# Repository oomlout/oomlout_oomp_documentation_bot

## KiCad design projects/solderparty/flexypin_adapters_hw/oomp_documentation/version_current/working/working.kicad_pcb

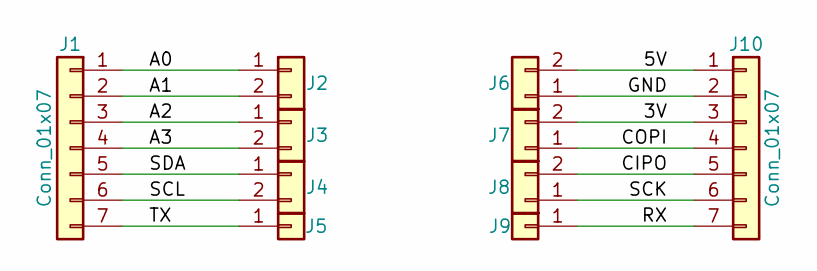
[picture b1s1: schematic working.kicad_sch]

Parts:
J1, J10: Conn_01x07; PinHeader_1x07_P2.54mm_Vertical
J2, J3, J4, J6, J7, J8: Conn_01x02; FlexyPin_1x02_P2.54mm
J5, J9: Conn_01x01; FlexyPin_1x01_P2.54mm

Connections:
/3V: J7.2, J10.3
/5V: J6.2, J10.1
/A0: J1.1, J2.1
/A1: J1.2, J2.2
/A2: J1.3, J3.1
/A3: J1.4, J3.2
/CIPO: J8.2, J10.5
/COPI: J7.1, J10.4
/GND: J6.1, J10.2
/RX: J9.1, J10.7
/SCK: J8.1, J10.6
/SCL: J1.6, J4.2
/SDA: J1.5, J4.1
/TX: J1.7, J5.1

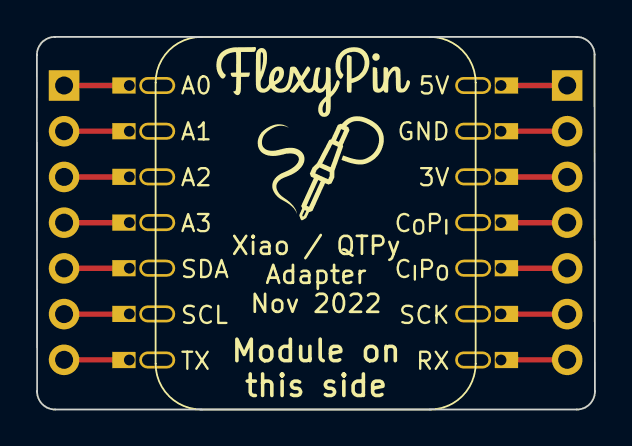
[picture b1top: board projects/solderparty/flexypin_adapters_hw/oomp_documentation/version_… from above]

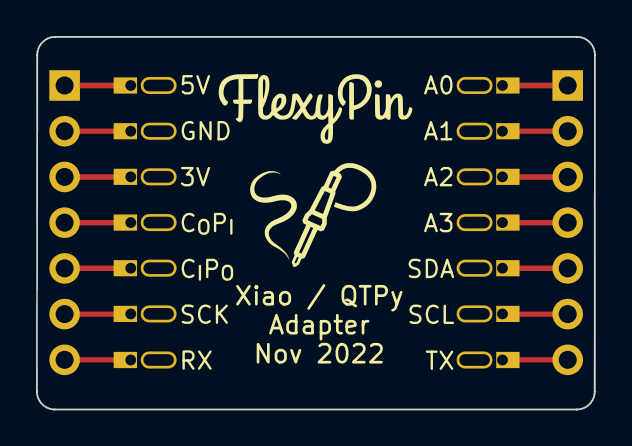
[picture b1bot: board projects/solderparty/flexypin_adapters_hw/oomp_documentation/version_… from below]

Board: 2 copper layers, 31.0 x 20.7 mm, 10 parts (2 on the bottom side), 14 nets.

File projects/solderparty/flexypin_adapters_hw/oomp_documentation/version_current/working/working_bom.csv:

"Id";"Designator";"Footprint";"Quantity";"Designation";"Supplier and ref";
1;"J4,J8,J7,J2,J3,J6";"FlexyPin_1x02_P2.54mm";6;"Conn_01x02";;;
2;"REF**";"Fiducial_0.5mm_Mask1.5mm";1;"Fiducial_0.5mm_Mask1.5mm";;;
3;"J5,J9";"FlexyPin_1x01_P2.54mm";2;"Conn_01x01";;;
4;"G***,G***";"SolderParty-New-Logo_7.5x6.4mm_SilkScreen";2;"LOGO";;;
5;"J10,J1";"PinHeader_1x07_P2.54mm_Vertical";2;"Conn_01x07";;;

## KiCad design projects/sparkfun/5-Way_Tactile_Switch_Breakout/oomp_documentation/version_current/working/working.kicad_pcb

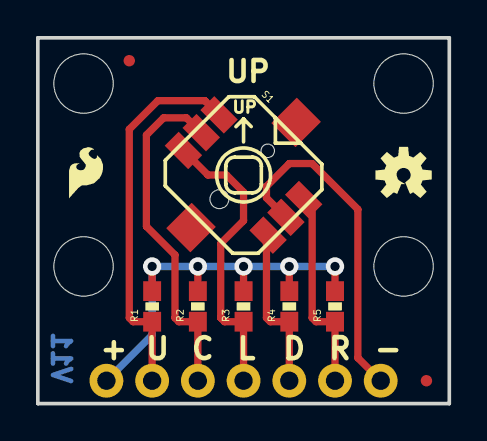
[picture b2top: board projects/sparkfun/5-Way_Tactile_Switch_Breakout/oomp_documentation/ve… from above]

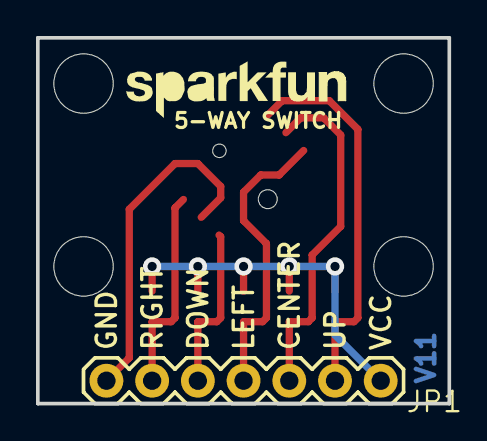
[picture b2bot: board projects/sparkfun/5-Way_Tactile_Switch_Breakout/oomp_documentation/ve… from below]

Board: 2 copper layers, 22.9 x 20.3 mm, 17 parts (2 on the bottom side), 7 nets.

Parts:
JP1: 1X07
JP2, JP7: FIDUCIALUFIDUCIAL; MICRO-FIDUCIAL
JP3, JP4, JP5, JP6: STAND-OFF
JP9: LOGO-SFESK; SFE-LOGO-FLAME
JP10: LOGO-SFENW2; SFE-NEW-WEB
R1, R2, R3, R4, R5: 10K; 0603-RES
S1: 5-WAY-TACTILE-SWITCH; JOYSTICK_MINI
U$1: OSHW-LOGOS; OSHW-LOGO-S
U$2: CREATIVE_COMMONS

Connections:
CENTER: JP1.3, R2.1, S1.CTR
DOWN: JP1.5, R4.1, S1.D
GND: JP1.7, S1.GND
LEFT: JP1.4, R3.1, S1.C
RIGHT: JP1.6, R5.1, S1.B
UP: JP1.2, R1.1, S1.A
VCC: JP1.1, R1.2, R2.2, R3.2, R4.2, R5.2

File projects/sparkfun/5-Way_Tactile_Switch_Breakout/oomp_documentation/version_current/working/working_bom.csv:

"Id";"Designator";"Footprint";"Quantity";"Designation";"Supplier and ref";
1;"JP7,JP2";"MICRO-FIDUCIAL";2;"FIDUCIALUFIDUCIAL";;;
2;"R3,R1,R2,R5,R4";"0603-RES";5;"10K";;;
3;"U$1";"OSHW-LOGO-S";1;"OSHW-LOGOS";;;
4;"U$2";"CREATIVE_COMMONS";1;"CREATIVE_COMMONS";;;
5;"JP5,JP6,JP3,JP4";"STAND-OFF";4;"STAND-OFF";;;
6;"JP9";"SFE-LOGO-FLAME";1;"LOGO-SFESK";;;
7;"S1";"JOYSTICK_MINI";1;"5-WAY-TACTILE-SWITCH";;;
8;"JP1";"1X07";1;"";;;
9;"JP10";"SFE-NEW-WEB";1;"LOGO-SFENW2";;;

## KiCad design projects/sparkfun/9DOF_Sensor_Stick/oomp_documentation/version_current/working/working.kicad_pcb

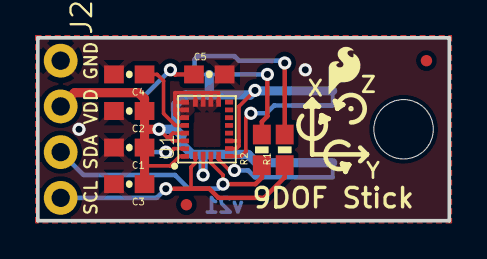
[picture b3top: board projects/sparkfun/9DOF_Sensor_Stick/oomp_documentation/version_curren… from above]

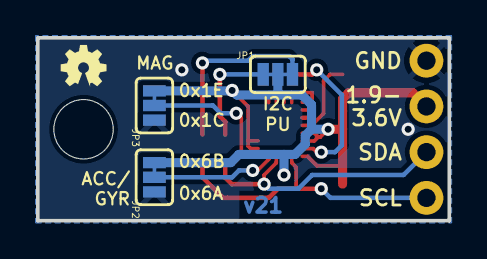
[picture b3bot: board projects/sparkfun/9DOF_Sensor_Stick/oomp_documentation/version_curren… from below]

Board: 2 copper layers, 22.9 x 10.2 mm, 18 parts (4 on the bottom side), 10 nets.

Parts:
C1: 10uF; 0603-CAP
C2, C3, C5: 0.1uF; 0603-CAP
C4: 10nF; 0603-CAP
FD3, FD4: FIDUCIALUFIDUCIAL; MICRO-FIDUCIAL
FRAME1: FRAME-LETTER; CREATIVE_COMMONS
H1: STAND-OFF
J2: 1X04_NO_SILK_ALL_ROUND
JP1: PAD-JUMPER-3-3OF3_NC_BY_TRACE_YES_SILK_FULL_BOX
JP2, JP3: PAD-JUMPER-3-2OF3_NC_BY_TRACE_YES_SILK_FULL_BOX
LOGO1: SFE_LOGO_FLAME.1_INCH; SFE_LOGO_FLAME_.1
LOGO3: OSHW-LOGOMINI; OSHW-LOGO-MINI
R1, R2: 4.7K; 0603-RES
U1: LSM9DS1; LGA24-8X4

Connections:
GND: C1.2, C2.2, C3.2, C4.2, C5.2, J2.1, JP2.1, JP3.1, U1.14, U1.15, U1.16, U1.17, U1.18, U1.19, U1.20
unnamed: JP1.1, R2.2
unnamed: JP1.3, R1.2
unnamed: C4.1, U1.21
unnamed: C5.1, U1.24
SCL: J2.4, R1.1, U1.2
SDA: J2.3, R2.1, U1.4
SDO_A/G: JP2.2, U1.5
SDO_M: JP3.2, U1.6
VDD: C1.1, C2.1, C3.1, J2.2, JP1.2, JP2.3, JP3.3, U1.1, U1.3, U1.7, U1.8, U1.22, U1.23

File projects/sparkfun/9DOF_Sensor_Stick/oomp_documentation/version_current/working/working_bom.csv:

"Id";"Designator";"Footprint";"Quantity";"Designation";"Supplier and ref";
1;"R2,R1";"0603-RES";2;"4.7K";;;
2;"C3,C2,C5";"0603-CAP";3;"0.1uF";;;
3;"FRAME1";"CREATIVE_COMMONS";1;"FRAME-LETTER";;;
4;"FD3,FD4";"MICRO-FIDUCIAL";2;"FIDUCIALUFIDUCIAL";;;
5;"LOGO1";"SFE_LOGO_FLAME_.1";1;"SFE_LOGO_FLAME.1_INCH";;;
6;"U1";"LGA24-8X4";1;"LSM9DS1";;;
7;"J2";"1X04_NO_SILK_ALL_ROUND";1;"";;;
8;"C1";"0603-CAP";1;"10uF";;;
9;"C4";"0603-CAP";1;"10nF";;;
10;"H1";"STAND-OFF";1;"STAND-OFF";;;
11;"LOGO3";"OSHW-LOGO-MINI";1;"OSHW-LOGOMINI";;;
12;"JP1";"PAD-JUMPER-3-3OF3_NC_BY_TRACE_YES_SILK_FULL_BOX";1;"";;;
13;"JP3,JP2";"PAD-JUMPER-3-2OF3_NC_BY_TRACE_YES_SILK_FULL_BOX";2;"";;;

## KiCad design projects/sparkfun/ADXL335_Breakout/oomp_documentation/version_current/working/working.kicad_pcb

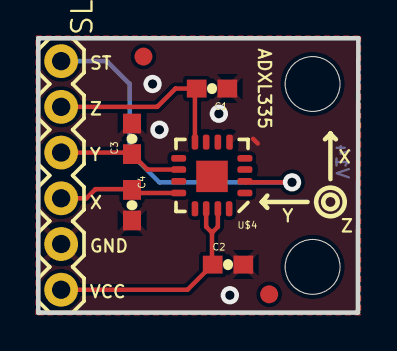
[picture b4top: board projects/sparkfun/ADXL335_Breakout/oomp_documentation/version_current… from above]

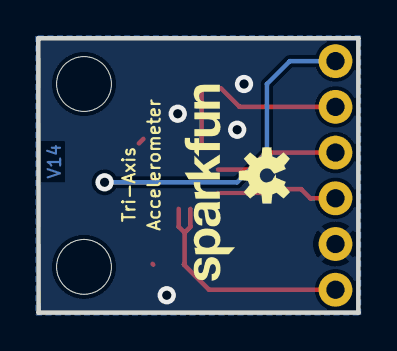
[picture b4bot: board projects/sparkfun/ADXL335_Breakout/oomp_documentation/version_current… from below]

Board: 16 copper layers, 17.8 x 15.2 mm, 12 parts (2 on the bottom side), 6 nets.

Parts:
C1, C2, C3, C4: 0.1uF; 0603-CAP
SL1: 1X06
U$1, U$3: FIDUCIAL1X2; FIDUCIAL-1X2
U$4: ADXL335-PATRICK""; ADXL335-P
U$5: OSHW-LOGO-S
U$6, U$7: STAND-OFF-TIGHT
U$8: SFE_LOGO_NAME_.1

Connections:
GND: C1.1, C2.2, C3.2, C4.2, SL1.5, U$4.3, U$4.5, U$4.6, U$4.7
ST: SL1.1, U$4.2
VCC: C2.1, SL1.6, U$4.14, U$4.15
XOUT: C4.1, SL1.4, U$4.12
YOUT: C3.1, SL1.3, U$4.10
ZOUT: C1.2, SL1.2, U$4.8

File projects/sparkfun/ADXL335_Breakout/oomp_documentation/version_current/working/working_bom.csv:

"Id";"Designator";"Footprint";"Quantity";"Designation";"Supplier and ref";
1;"C4,C3,C1,C2";"0603-CAP";4;"0.1uF";;;
2;"U$7,U$6";"STAND-OFF-TIGHT";2;"";;;
3;"U$3,U$1";"FIDUCIAL-1X2";2;"FIDUCIAL1X2";;;
4;"U$4";"ADXL335-P";1;"ADXL335-PATRICK""";;;
5;"SL1";"1X06";1;"";;;
6;"U$8";"SFE_LOGO_NAME_.1";1;"";;;
7;"U$5";"OSHW-LOGO-S";1;"";;;

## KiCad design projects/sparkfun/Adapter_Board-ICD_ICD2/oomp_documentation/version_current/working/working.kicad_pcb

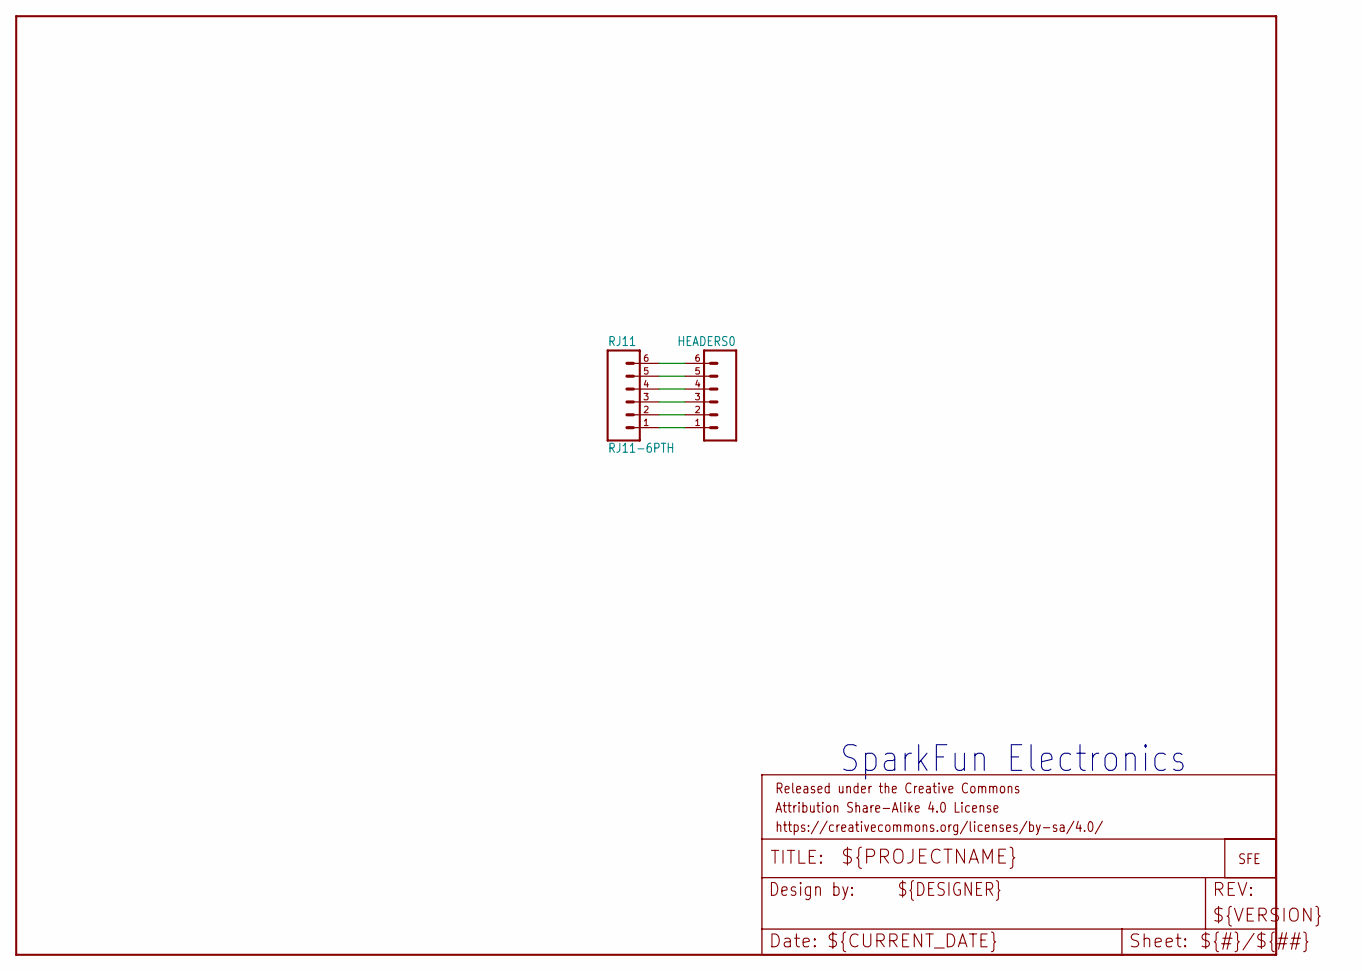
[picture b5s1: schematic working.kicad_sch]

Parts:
FRAME1: FRAME-LETTERNO_PACKAGE; DUMMY
HEADERS0: M06POLAR; MOLEX-1X6
JP1: LOGO-SFESK; SFE-LOGO-FLAME
RJ11: RJ11-6PTH; RJ11-6

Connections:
unnamed: HEADERS0.6, RJ11.6
unnamed: HEADERS0.1, RJ11.1
unnamed: HEADERS0.2, RJ11.2
unnamed: HEADERS0.3, RJ11.3
unnamed: HEADERS0.4, RJ11.4
unnamed: HEADERS0.5, RJ11.5

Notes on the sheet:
SparkFun Electronics

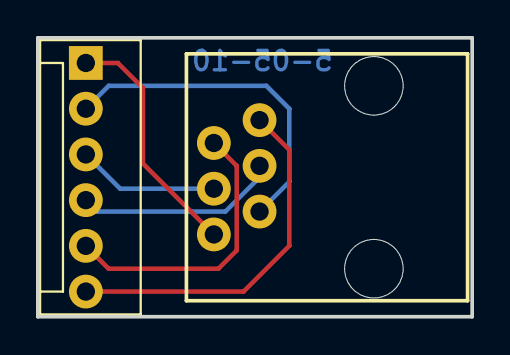
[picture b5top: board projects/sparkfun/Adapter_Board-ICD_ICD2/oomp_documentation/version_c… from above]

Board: 16 copper layers, 24.1 x 15.5 mm, 4 parts (1 on the bottom side), 6 nets.

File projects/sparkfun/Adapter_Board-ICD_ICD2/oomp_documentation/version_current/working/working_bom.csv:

"Id";"Designator";"Footprint";"Quantity";"Designation";"Supplier and ref";
1;"RJ11";"RJ11-6";1;"RJ11-6PTH";;;
2;"FRAME1";"DUMMY";1;"";;;
3;"HEADERS0";"MOLEX-1X6";1;"";;;
4;"JP1";"SFE-LOGO-FLAME";1;"LOGO-SFESK";;;

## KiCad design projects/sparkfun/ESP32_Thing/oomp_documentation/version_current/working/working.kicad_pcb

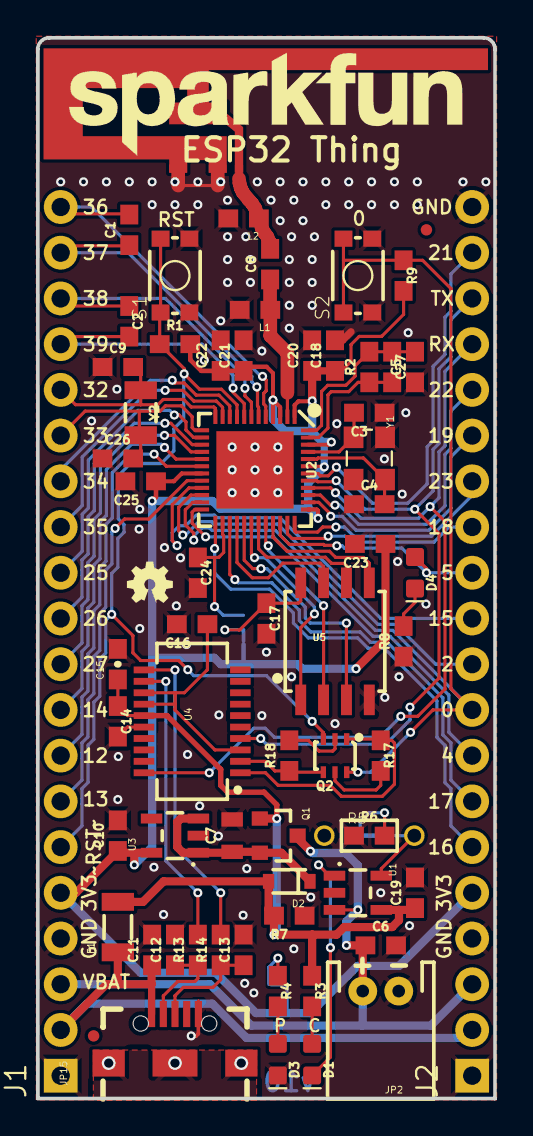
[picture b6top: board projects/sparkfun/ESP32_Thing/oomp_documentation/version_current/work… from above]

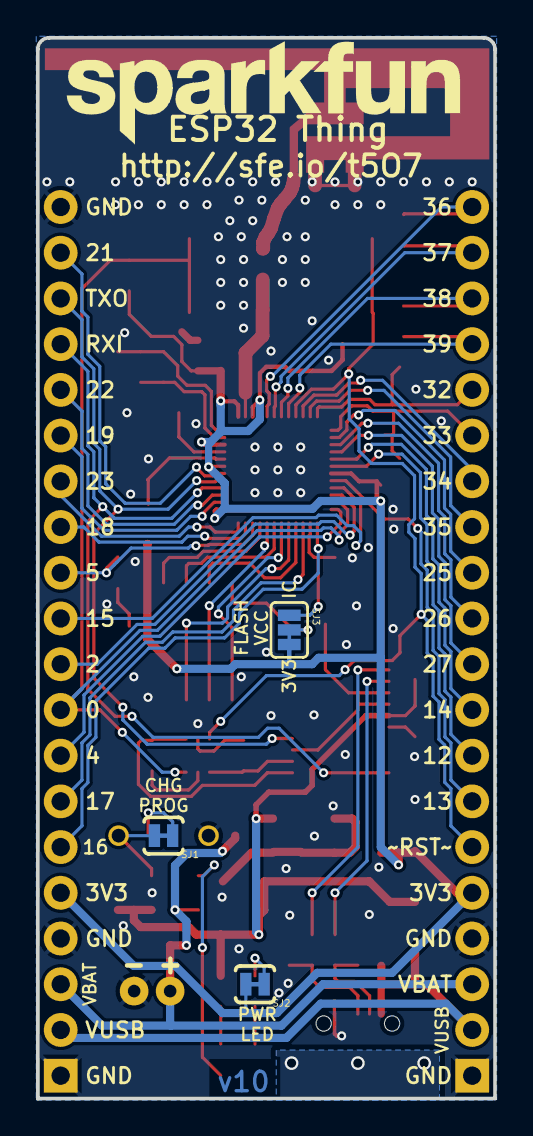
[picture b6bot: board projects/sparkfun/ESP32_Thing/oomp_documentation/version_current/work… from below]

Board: 2 copper layers, 25.4 x 58.9 mm, 72 parts (4 on the bottom side), 66 nets.

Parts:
C1, C2: 270pF; 0603
C3, C4: 10pF; 0603
C5: 10nF; 0603
C6, C19: 4.7uF; 0603
C7: 1.0uF; 0805
C8: 5.6pF; 0603
C9, C26: 15pF; 0603
C10: 2.2uF; 0603
C11, C14, C16, C17, C20, C21, C23, C25: 0.1uF; 0603
C12, C13: 47pF; 0603
C15: 4.7uF; 0603-CAP
C18: 100pF; 0603
C22: 10uF; 0603
C24: 1.0uF; 0603
C27: 3.0nF; 0603
D1: Yellow; LED-0603
D2: BAT20J; SOD-323
D3: RED; LED-0603
D4: BLUE; LED-0603
E1: ANTENNA; TRACE_ANTENNA_2.4GHZ_25.7MM_TUNED
F1: 500mA; PTC-1206
FD1, FD2: FIDUCIALUFIDUCIAL; MICRO-FIDUCIAL
FRAME1: FRAME-LEDGER; CREATIVE_COMMONS
J1, J2: 1X20_NOSILK
JP2: LiPo; JST-2-PTH
JP15: USB-B-MICRO-SMD_V03
L1, L2: DNP; 0603
LOGO1, LOGO3: SFE_LOGO_NAME.2_INCH; SFE_LOGO_NAME_.2
LOGO2: OSHW-LOGOMINI; OSHW-LOGO-MINI
Q1: 2.5A/30V; SOT23-3
Q2: MBT3904DW1T1; SC70-6
R1, R7, R9, R17, R18: 10k; 0603
R2: 20k; 0603
R3, R4: 1K; 0603
R5: DNP; 1_6W-RES
R6: 2.0k; 0603
R8: 330; 0603
R13, R14: 27; 0603
S1: RESET; TACTILE_SWITCH_SMD_4.6X2.8MM
S2: BTN-0; TACTILE_SWITCH_SMD_4.6X2.8MM
SJ1, SJ2: JUMPER-PAD-2-NC_BY_TRACE; PAD-JUMPER-2-NC_BY_TRACE_YES_SILK
SJ3: PAD-JUMPER-3-2OF3_NC_BY_TRACE_YES_SILK_FULL_BOX
U1: MCP73831; SOT23-5
U2: ESP3212; QFN48-0.4MM
U3: AP2112K-3.3V; SOT23-5
U4: FT231XS; SSOP20_L
U5: W25Q32FVSS; SOIC-8
Y1: 26MHz; CRYSTAL-SMD-3.2X2.5
Y2: 32.768kHz; CRYSTAL-SMD-3.2X1.5MM

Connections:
0: J2.9, Q2.6, R9.1, S2.3, S2.4, U2.23
2: J2.10, U2.22
3.3V: C10.1, C18.1, C20.1, C21.1, C22.1, C23.1, C25.1, J1.5, J2.5, R1.2, R9.2, SJ2.2, SJ3.3, U2.1, U2.3, U2.4, U2.19, U2.37, U2.43, U2.46, U3.5
3.3V_F: C16.1, U4.3, U4.13, U4.14
4: J2.8, U2.24
5: D4.A, J2.12, U2.34
12: J1.8, U2.18
13: J1.7, U2.20
14: J1.9, U2.17
15: J2.11, U2.21
16: J2.6, U2.25
17: J2.7, U2.27
18: J2.13, U2.35
19: J2.15, U2.38
21: J2.19, U2.42
22: J2.16, U2.39
23: J2.14, U2.36
25: J1.12, U2.14
26: J1.11, U2.15
27: J1.10, U2.16
32K_XN: C26.2, J1.15, U2.13, Y2.P$2
32K_XP: C9.2, J1.16, U2.12, Y2.P$1
34: J1.14, U2.10
35: J1.13, U2.11
36: C1.2, J1.20, U2.5
37: C1.1, J1.19, U2.6
38: C2.1, J1.18, U2.7
39: C2.2, J1.17, U2.8
CAP_10N: C5.2, C27.1, R2.2, U2.48
CHIP_PU: J1.6, Q2.3, R1.1, S1.3, S1.4, U2.9
D+: C13.1, JP15.D+, R14.1
D-: C12.1, JP15.D-, R13.1
DTR: Q2.1, R17.1, U4.1
FLASH_SCK: U2.31, U5.6
FLASH_SCS: U2.30, U5.1
FLASH_SDI: U2.33, U5.5
FLASH_SDO: U2.32, U5.2
FLASH_SHD: U2.28, U5.7
FLASH_SWP: U2.29, U5.3
FLASH_VDD: C24.1, SJ3.1, U2.26
GND: C3.1, C4.1, C5.1, C6.2, C7.2, C9.1, C10.2, C11.2, C12.2, C13.2, C14.2, C15.2, C16.2, C17.2, C18.2, C19.2, C20.2, C21.2, C22.2, C23.2, C24.2, C25.2, C26.1, D3.C, E1.GND, E1.GND2, J1.1, J1.4, J2.1, J2.4, J2.20, JP2.1, JP15.GND, L1.2, L2.2, R5.1, R6.1, R7.1, R8.1, S1.1, S1.2, S2.1, S2.2, U1.2, U2.EP, U3.2, U4.6, U4.16, U5.4, Y1.2, Y1.4
LNA_IN: C8.1, L1.1, U2.2
unnamed: D4.C, R8.2
unnamed: D3.A, R4.2
unnamed: R4.1, SJ2.1
unnamed: C27.2, R2.1, U2.47
unnamed: R13.2, U4.12
unnamed: R14.2, U4.11
unnamed: D1.C, U1.1
unnamed: Q2.5, R17.2
unnamed: C17.1, SJ3.2, U5.8
unnamed: Q2.2, R18.2
unnamed: C3.2, U2.45, Y1.1
unnamed: R5.2, SJ1.2, U1.5
unnamed: C4.2, U2.44, Y1.3
unnamed: R6.2, SJ1.1
unnamed: D1.A, R3.2
RTS: Q2.4, R18.1, U4.2
SHIELD: JP15.SHIELD1, JP15.SHIELD2, JP15.SHIELD3
TRACE_ANT: C8.2, E1.ANT, L2.1
U0RXD: J2.17, U2.40, U4.20
U0TXD: J2.18, U2.41, U4.4
VIN: C7.1, D2.C, Q1.2, U3.1, U3.3
VUSB-RAW: C11.1, F1.1, J1.2, J2.2, JP15.VBUS
V_BATT: C6.1, J1.3, J2.3, JP2.2, Q1.3, U1.3
V_USB: C14.1, C15.1, C19.1, D2.A, F1.2, Q1.1, R3.1, R7.2, U1.4, U4.15

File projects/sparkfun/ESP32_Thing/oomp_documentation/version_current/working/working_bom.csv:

"Id";"Designator";"Footprint";"Quantity";"Designation";"Supplier and ref";
1;"R3,R4";"0603";2;"1K";;;
2;"U5";"SOIC-8";1;"W25Q32FVSS";;;
3;"C10";"0603";1;"2.2uF";;;
4;"R1,R9,R17,R7,R18";"0603";5;"10k";;;
5;"JP15";"USB-B-MICRO-SMD_V03";1;"";;;
6;"R14,R13";"0603";2;"27";;;
7;"C20,C14,C25,C17,C16,C23,C11,C21";"0603";8;"0.1uF";;;
8;"C13,C12";"0603";2;"47pF";;;
9;"C8";"0603";1;"5.6pF";;;
10;"C26,C9";"0603";2;"15pF";;;
11;"C1,C2";"0603";2;"270pF";;;
12;"C19,C6";"0603";2;"4.7uF";;;
13;"C18";"0603";1;"100pF";;;
14;"L2,L1";"0603";2;"DNP";;;
15;"J1,J2";"1X20_NOSILK";2;"";;;
16;"R5";"1_6W-RES";1;"DNP";;;
17;"C3,C4";"0603";2;"10pF";;;
18;"Y2";"CRYSTAL-SMD-3.2X1.5MM";1;"32.768kHz";;;
19;"C22";"0603";1;"10uF";;;
20;"Q1";"SOT23-3";1;"2.5A/30V";;;
21;"C15";"0603-CAP";1;"4.7uF";;;
22;"C27";"0603";1;"3.0nF";;;
23;"U1";"SOT23-5";1;"MCP73831";;;
24;"S2";"TACTILE_SWITCH_SMD_4.6X2.8MM";1;"BTN-0";;;
25;"FD2,FD1";"MICRO-FIDUCIAL";2;"FIDUCIALUFIDUCIAL";;;
26;"D4";"LED-0603";1;"BLUE";;;
27;"F1";"PTC-1206";1;"500mA";;;
28;"C7";"0805";1;"1.0uF";;;
29;"U3";"SOT23-5";1;"AP2112K-3.3V";;;
30;"R2";"0603";1;"20k";;;
31;"E1";"TRACE_ANTENNA_2.4GHZ_25.7MM_TUNED";1;"ANTENNA";;;
32;"D3";"LED-0603";1;"RED";;;
33;"Q2";"SC70-6";1;"MBT3904DW1T1";;;
34;"LOGO2";"OSHW-LOGO-MINI";1;"OSHW-LOGOMINI";;;
35;"D1";"LED-0603";1;"Yellow";;;
36;"R8";"0603";1;"330";;;
37;"S1";"TACTILE_SWITCH_SMD_4.6X2.8MM";1;"RESET";;;
38;"U4";"SSOP20_L";1;"FT231XS";;;
39;"U2";"QFN48-0.4MM";1;"ESP3212";;;
40;"JP2";"JST-2-PTH";1;"LiPo";;;
41;"Y1";"CRYSTAL-SMD-3.2X2.5";1;"26MHz";;;
42;"FRAME1";"CREATIVE_COMMONS";1;"FRAME-LEDGER";;;
43;"R6";"0603";1;"2.0k";;;
44;"LOGO1,LOGO3";"SFE_LOGO_NAME_.2";2;"SFE_LOGO_NAME.2_INCH";;;
45;"C24";"0603";1;"1.0uF";;;
46;"C5";"0603";1;"10nF";;;
47;"D2";"SOD-323";1;"BAT20J";;;
48;"SJ3";"PAD-JUMPER-3-2OF3_NC_BY_TRACE_YES_SILK_FULL_BOX";1;"";;;
49;"SJ1,SJ2";"PAD-JUMPER-2-NC_BY_TRACE_YES_SILK";2;"JUMPER-PAD-2-NC_BY_TRACE";;;

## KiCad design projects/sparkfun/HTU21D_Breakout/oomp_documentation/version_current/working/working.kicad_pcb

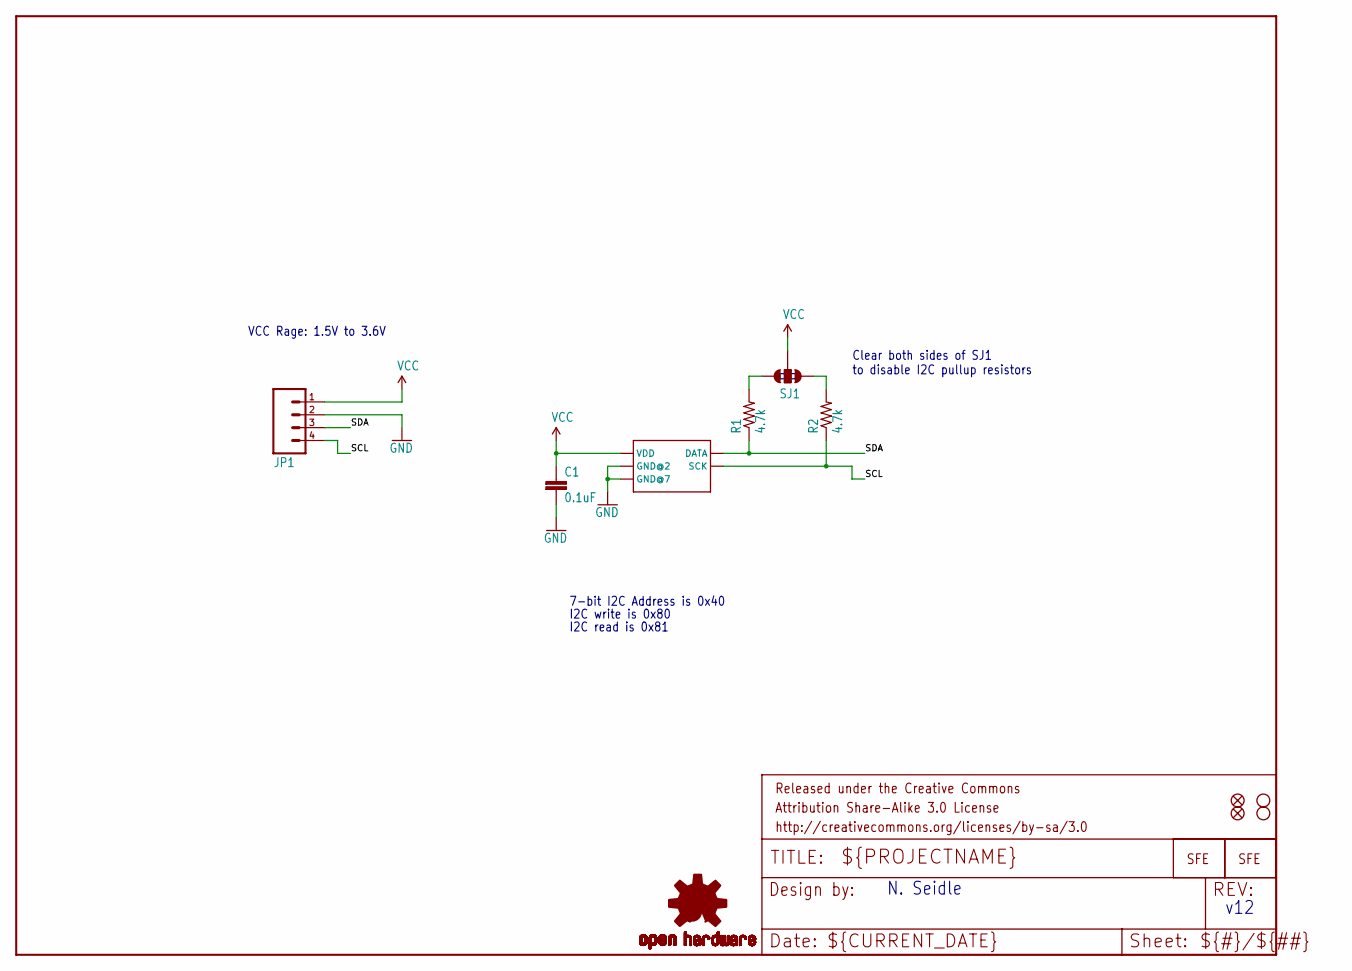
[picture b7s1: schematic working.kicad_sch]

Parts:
C1: 0.1uF; 0603-CAP
FRAME2: FRAME-LETTER; CREATIVE_COMMONS
JP1: M04PTH; 1X04
JP2: LOGO-SFENW2; SFE-NEW-WEB
JP3, JP4: FIDUCIALUFIDUCIAL; MICRO-FIDUCIAL
LOGO1: LOGO-SFESK; SFE-LOGO-FLAME
LOGO2: OSHW-LOGOS; OSHW-LOGO-S
R1, R2: 4.7k; 0603-RES
SJ1: SOLDERJUMPER_2WAYPASTE1&2&3; SJ_3_PASTE1&2&3
STANDOFF1, STANDOFF2: STAND-OFF
U1: HTU21DSMD; HTU21D

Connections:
3.3V: C1.1, JP1.1, SJ1.2, U1.VDD
GND: C1.2, JP1.2, U1.7 (GND@7), U1.GND (GND@2)
unnamed: R1.2, SJ1.3
unnamed: R2.2, SJ1.1
SCL: JP1.4, R2.1, U1.SCK
SDA: JP1.3, R1.1, U1.DATA

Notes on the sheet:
N. Seidle
I2C read is 0x81
I2C write is 0x80
VCC Rage: 1.5V to 3.6V
Clear both sides of SJ1 to disable I2C pullup resistors
7-bit I2C Address is 0x40
v12

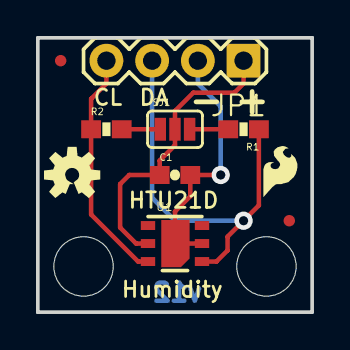
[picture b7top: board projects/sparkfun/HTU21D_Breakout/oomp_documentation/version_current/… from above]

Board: 2 copper layers, 15.2 x 15.2 mm, 14 parts (1 on the bottom side), 6 nets.

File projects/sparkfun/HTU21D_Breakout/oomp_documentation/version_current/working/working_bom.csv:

"Id";"Designator";"Footprint";"Quantity";"Designation";"Supplier and ref";
1;"C1";"0603-CAP";1;"0.1uF";;;
2;"LOGO1";"SFE-LOGO-FLAME";1;"LOGO-SFESK";;;
3;"JP3,JP4";"MICRO-FIDUCIAL";2;"FIDUCIALUFIDUCIAL";;;
4;"JP1";"1X04";1;"";;;
5;"STANDOFF1,STANDOFF2";"STAND-OFF";2;"STAND-OFF";;;
6;"FRAME2";"CREATIVE_COMMONS";1;"FRAME-LETTER";;;
7;"U1";"HTU21D";1;"HTU21D";;;
8;"R2,R1";"0603-RES";2;"4.7k";;;
9;"SJ1";"SJ_3_PASTE1&2&3";1;"";;;
10;"LOGO2";"OSHW-LOGO-S";1;"OSHW-LOGOS";;;
11;"JP2";"SFE-NEW-WEB";1;"LOGO-SFENW2";;;

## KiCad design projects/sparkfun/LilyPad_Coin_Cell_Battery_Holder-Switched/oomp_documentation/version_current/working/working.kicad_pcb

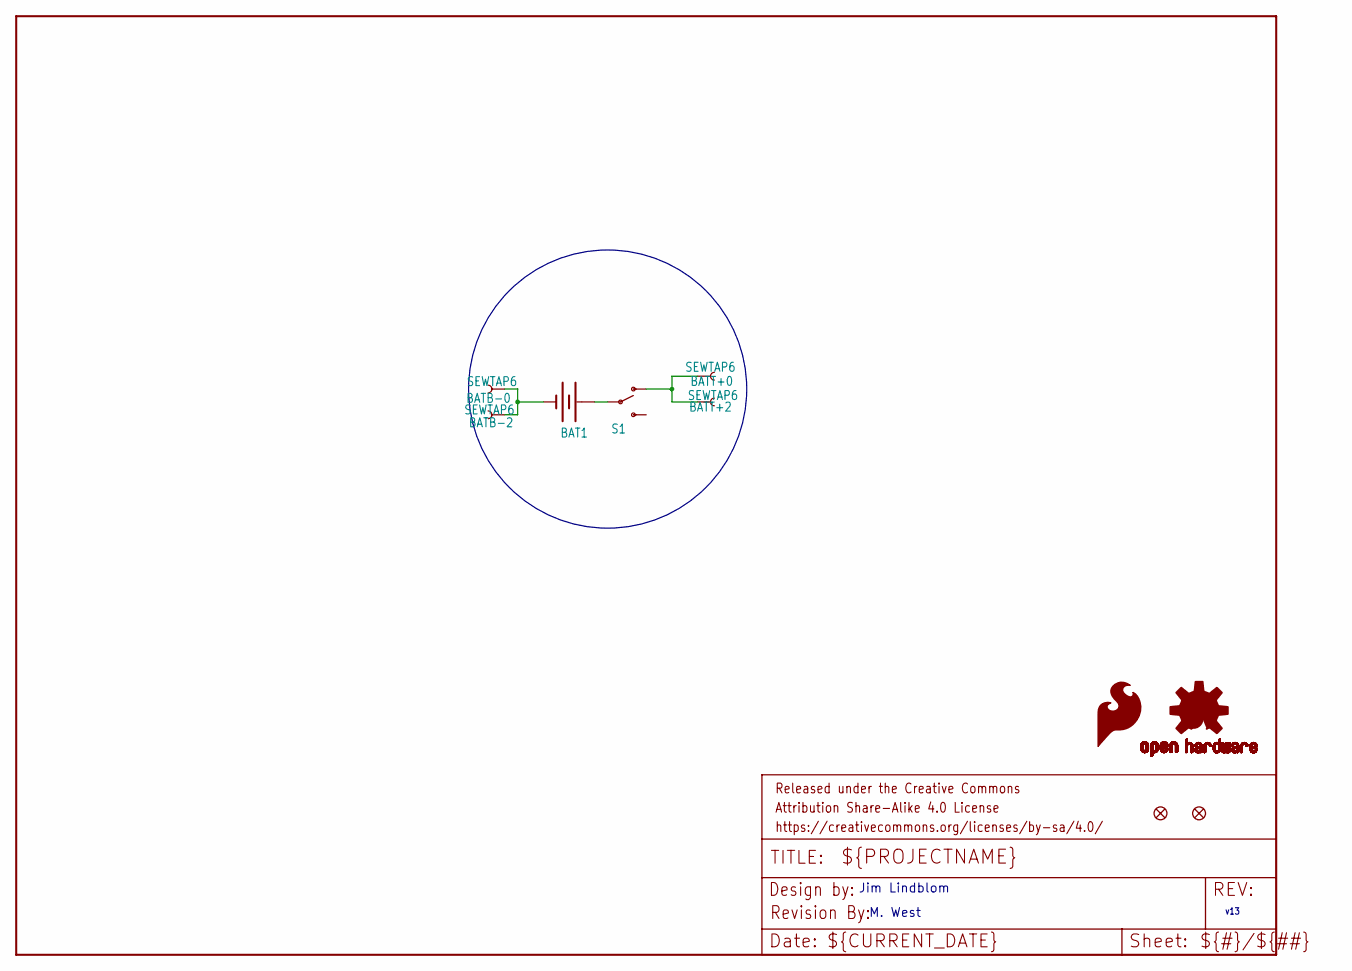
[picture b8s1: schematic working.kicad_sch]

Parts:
BAT1: 20mm coincell; BATTCON_20MM_4LEGS
BATB-0, BATB-2: SEWTAP6; PETAL-SMALL-2SIDE
BATT+0, BATT+2: SEWTAP6; PETAL-SMALL-2SIDE
FD1, FD2: FIDUCIALUFIDUCIAL; MICRO-FIDUCIAL
FRAME1: FRAME-LETTER; CREATIVE_COMMONS
LOGO1: SFE_LOGO_FLAME.1_INCH; SFE_LOGO_FLAME_.1
LOGO2: OSHW-LOGOS; OSHW-LOGO-S
S1: SWITCH-SPDTSMD; AYZ0202
U$1: REVISION

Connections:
GND: BAT1.NEGATIVE (-), BATB-0.1, BATB-2.1
unnamed: BAT1.POSITIVE@1 (+), BAT1.POSITIVE@2 (+), BAT1.POSITIVE@3 (+), BAT1.POSITIVE@4 (+), S1.2
unnamed: BATT+0.1, BATT+2.1, S1.1 (O)

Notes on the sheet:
v13
Jim Lindblom
M. West

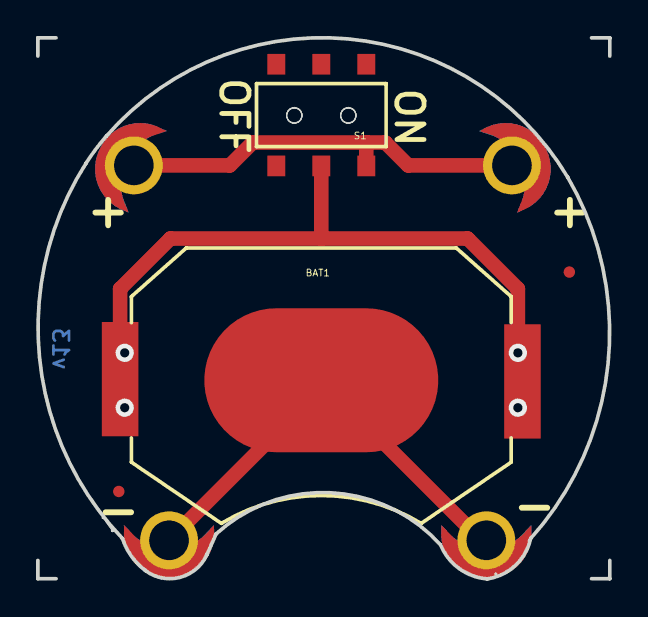
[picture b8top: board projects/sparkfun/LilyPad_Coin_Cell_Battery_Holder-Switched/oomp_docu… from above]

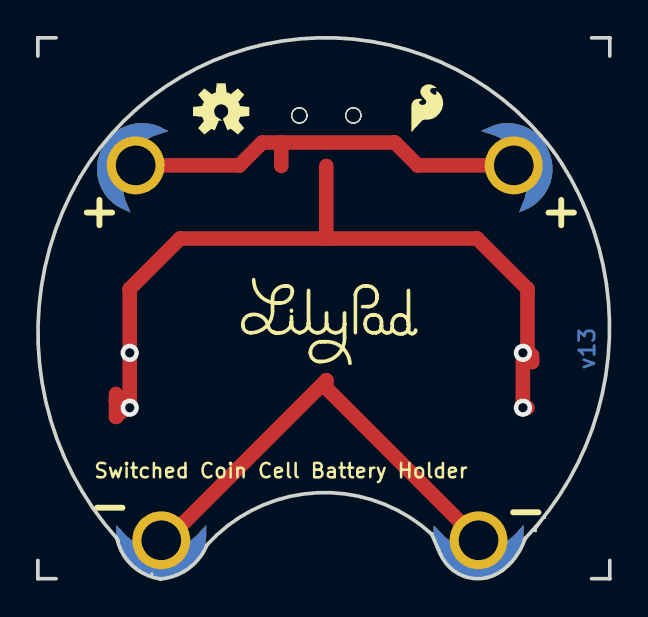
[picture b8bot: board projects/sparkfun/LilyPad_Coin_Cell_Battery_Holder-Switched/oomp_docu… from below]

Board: 2 copper layers, 31.7 x 30.1 mm, 13 parts (3 on the bottom side), 3 nets.

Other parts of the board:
U$3: LOGO-LILYPAD

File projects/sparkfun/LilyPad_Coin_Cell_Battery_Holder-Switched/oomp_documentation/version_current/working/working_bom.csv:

"Id";"Designator";"Footprint";"Quantity";"Designation";"Supplier and ref";
1;"U$1";"REVISION";1;"REVISION";;;
2;"BATB-0,BATT+2,BATT+0,BATB-2";"PETAL-SMALL-2SIDE";4;"SEWTAP6";;;
3;"FRAME1";"CREATIVE_COMMONS";1;"FRAME-LETTER";;;
4;"FD1,FD2";"MICRO-FIDUCIAL";2;"FIDUCIALUFIDUCIAL";;;
5;"S1";"AYZ0202";1;"";;;
6;"BAT1";"BATTCON_20MM_4LEGS";1;"20mm coincell";;;
7;"U$3";"LOGO-LILYPAD";1;"";;;
8;"LOGO1";"SFE_LOGO_FLAME_.1";1;"SFE_LOGO_FLAME.1_INCH";;;
9;"LOGO2";"OSHW-LOGO-S";1;"OSHW-LOGOS";;;

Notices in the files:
projects/sparkfun/Adapter_Board-ICD_ICD2/oomp_documentation/version_current/working/working.kicad_sch:
https://creativecommons.org/licenses/by-sa/4.0
Released under the Creative Commons
projects/sparkfun/HTU21D_Breakout/oomp_documentation/version_current/working/working.kicad_sch:
http://creativecommons.org/licenses/by-sa/3.0
parts and their libraries:
Released under the Creative Commons Attribution Share-Alike 3.0 License
Released under the Creative Commons Attribution Share-Alike 4.0 License
